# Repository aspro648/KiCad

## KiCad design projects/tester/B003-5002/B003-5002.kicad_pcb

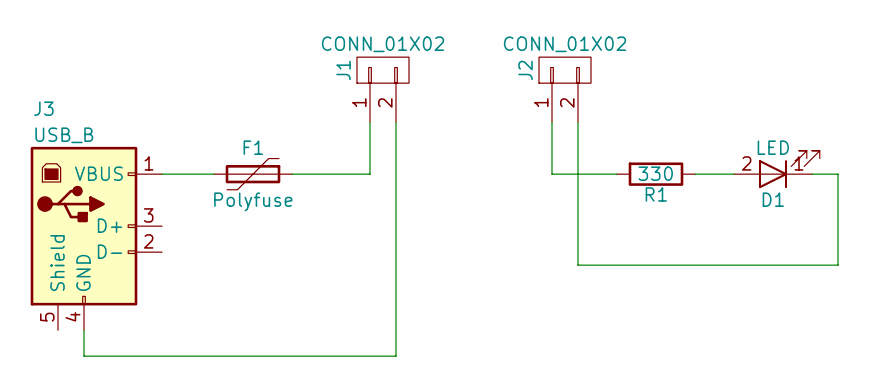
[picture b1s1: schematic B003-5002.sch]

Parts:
D1: LED; LED_D3.0mm
F1: Polyfuse; Fuse_Littelfuse-LVR100
J1: CONN_01X02; Molex_Microfit3_Header_02x01_Angled_43045-020x
J2: CONN_01X02; Molex_NanoFit_1x02x2.50mm_Angled
J3: USB_B
R1: 330; R_Axial_DIN0207_L6.3mm_D2.5mm_P7.62mm_Horizontal

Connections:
unnamed: D1.1 (K), J2.2
unnamed: D1.2 (A), R1.1
unnamed: F1.1, J1.1
unnamed: F1.2, J3.1 (VBUS)
unnamed: J1.2, J3.4 (GND)
unnamed: J2.1, R1.2

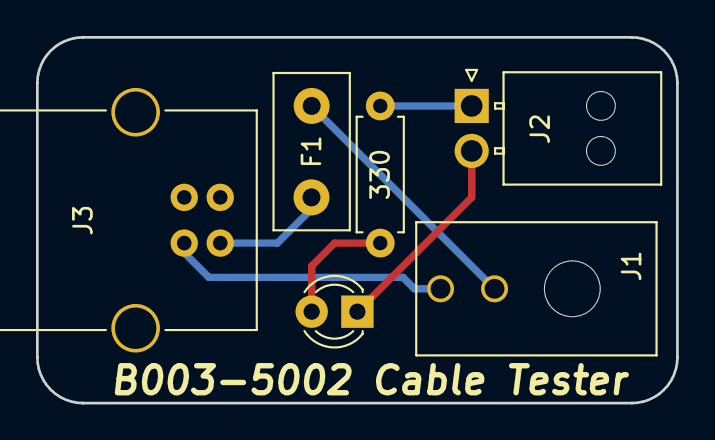
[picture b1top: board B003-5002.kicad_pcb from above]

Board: 2 copper layers, 35.6 x 20.3 mm, 6 parts (0 on the bottom side), 6 nets.

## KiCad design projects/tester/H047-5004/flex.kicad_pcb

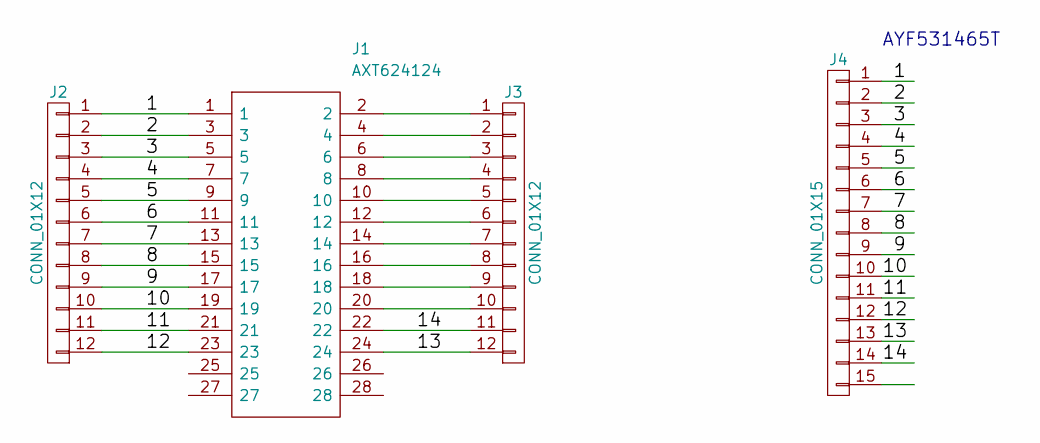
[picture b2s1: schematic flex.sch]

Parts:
J1: AXT624124; Mouser Part Number 769-AXT624124
J2, J3: CONN_01X12; Pin_Header_Straight_1x12_Pitch1.27mm
J4: CONN_01X15

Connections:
/1: J1.1, J2.1, J4.1
/2: J1.3, J2.2, J4.2
/3: J1.5, J2.3, J4.3
/4: J1.7, J2.4, J4.4
/5: J1.9, J2.5, J4.5
/6: J1.11, J2.6, J4.6
/7: J1.13, J2.7, J4.7
/8: J1.15, J2.8, J4.8
/9: J1.17, J2.9, J4.9
/10: J1.19, J2.10, J4.10
/11: J1.21, J2.11, J4.11
/12: J1.23, J2.12, J4.12
/13: J1.24, J3.12, J4.13
/14: J1.22, J3.11, J4.14
unnamed: J1.2, J3.1
unnamed: J1.4, J3.2
unnamed: J1.6, J3.3
unnamed: J1.8, J3.4
unnamed: J1.10, J3.5
unnamed: J1.12, J3.6
unnamed: J1.14, J3.7
unnamed: J1.16, J3.8
unnamed: J1.18, J3.9
unnamed: J1.20, J3.10

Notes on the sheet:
AYF531465T

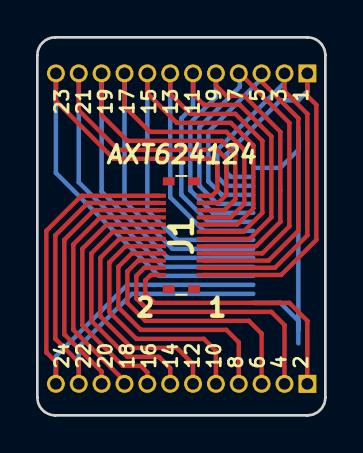
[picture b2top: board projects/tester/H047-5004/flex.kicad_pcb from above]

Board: 2 copper layers, 16.0 x 21.0 mm, 4 parts (1 on the bottom side), 24 nets.

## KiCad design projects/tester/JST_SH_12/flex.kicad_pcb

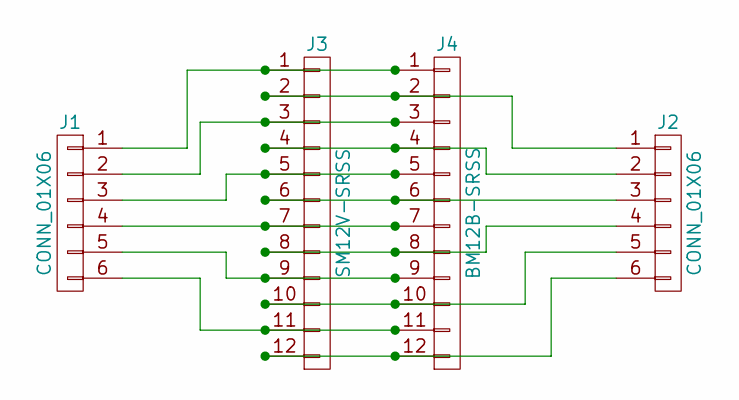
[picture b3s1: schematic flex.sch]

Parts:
J1, J2: CONN_01X06; Pin_Header_Straight_1x06_Pitch2.54mm
J3: SM12V-SRSS; JST_SH_SM12B-SRSS-TB_12x1.00mm_Angled
J4: BM12B-SRSS; JST_SH_BM12B-SRSS-TB_12x1.00mm_Straight

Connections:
unnamed: J1.1, J3.1, J4.1
unnamed: J1.2, J3.3, J4.3
unnamed: J1.3, J3.5, J4.5
unnamed: J1.4, J3.7, J4.7
unnamed: J1.5, J3.9, J4.9
unnamed: J1.6, J3.11, J4.11
unnamed: J2.1, J3.2, J4.2
unnamed: J2.2, J3.4, J4.4
unnamed: J2.3, J3.6, J4.6
unnamed: J2.4, J3.8, J4.8
unnamed: J2.5, J3.10, J4.10
unnamed: J2.6, J3.12, J4.12

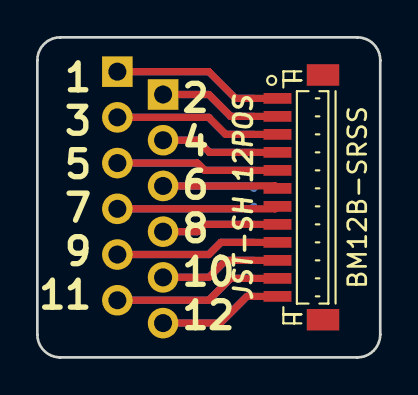
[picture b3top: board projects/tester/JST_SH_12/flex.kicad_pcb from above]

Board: 2 copper layers, 19.1 x 17.8 mm, 4 parts (1 on the bottom side), 12 nets.

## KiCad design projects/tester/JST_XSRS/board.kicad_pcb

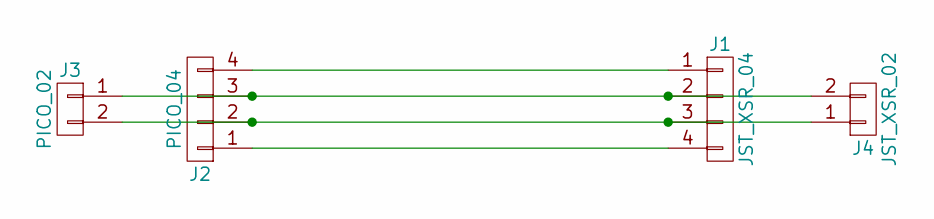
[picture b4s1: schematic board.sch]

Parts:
J1: JST_XSR_04; JST_SH_BM04B-SRSS-TB_04x1.00mm_Straight
J2: PICO_04; Molex_PicoBlade_53048-0410_04x1.25mm_Angled
J3: PICO_02; Molex_PicoBlade_53048-0210_02x1.25mm_Angled
J4: JST_XSR_02; JST_SH_BM02B-SRSS-TB_02x1.00mm_Straight

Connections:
unnamed: J1.1, J2.4
unnamed: J1.2, J2.3, J3.1, J4.2
unnamed: J1.3, J2.2, J3.2, J4.1
unnamed: J1.4, J2.1

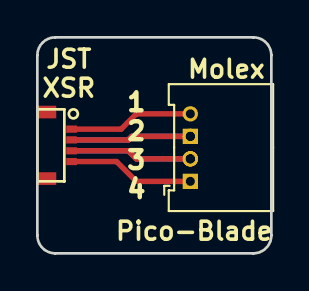
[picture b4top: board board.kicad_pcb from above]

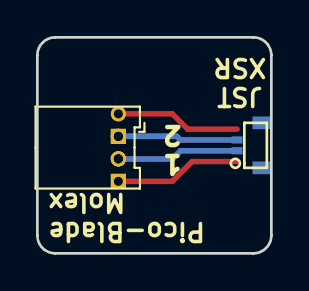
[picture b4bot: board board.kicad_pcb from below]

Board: 2 copper layers, 13.0 x 12.0 mm, 4 parts (2 on the bottom side), 4 nets.

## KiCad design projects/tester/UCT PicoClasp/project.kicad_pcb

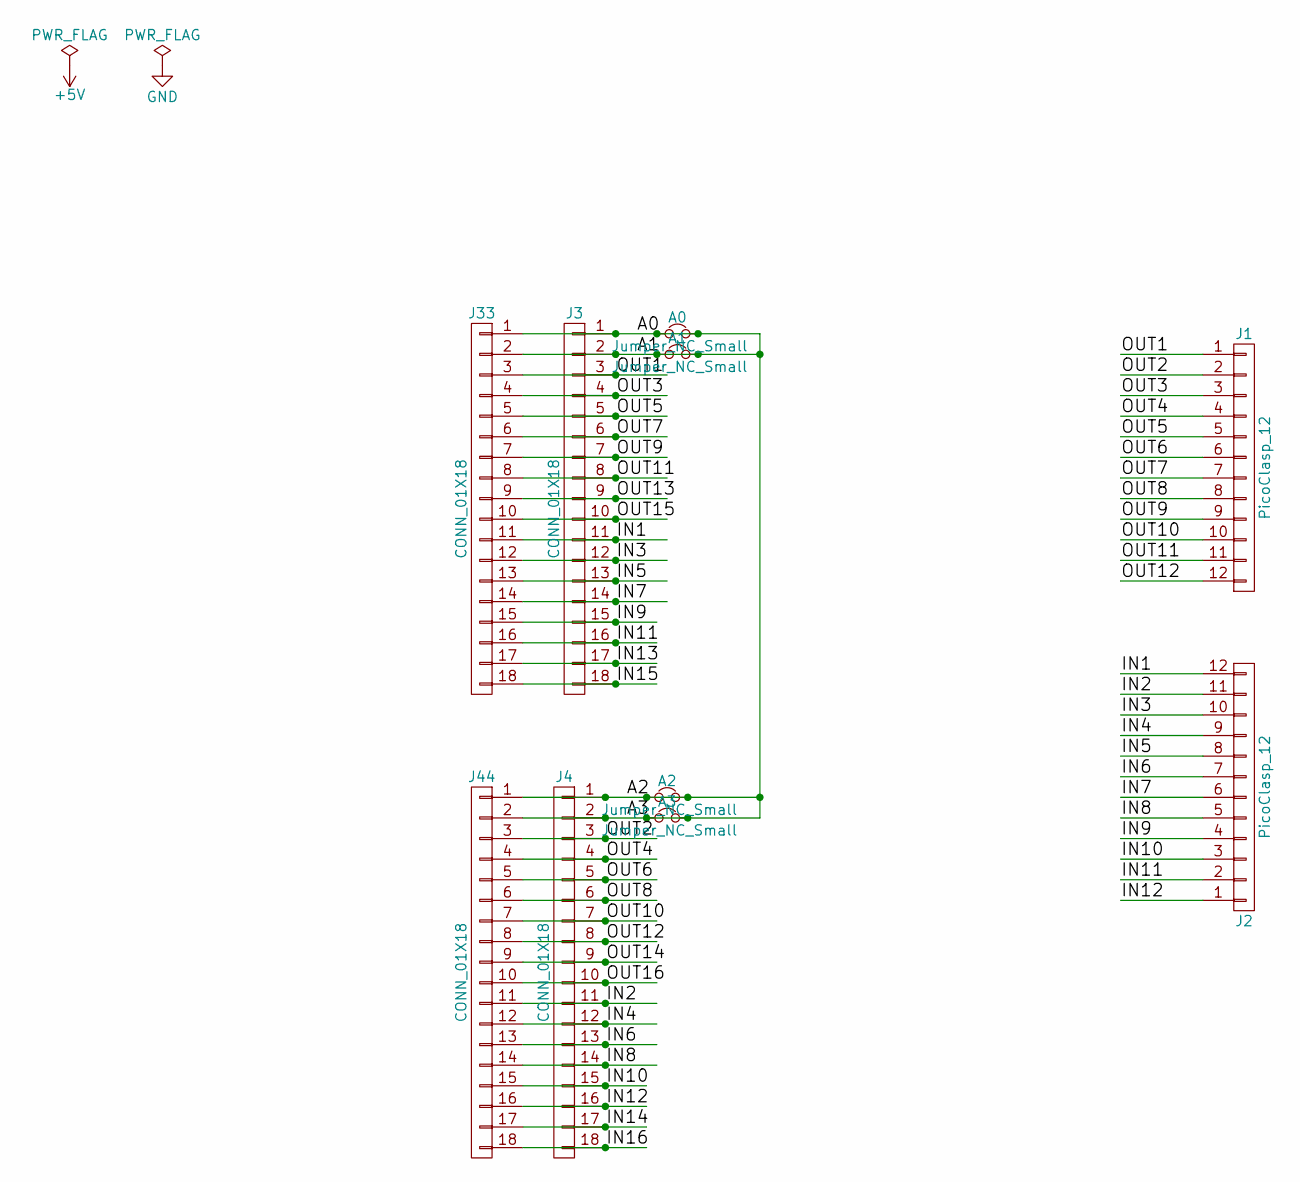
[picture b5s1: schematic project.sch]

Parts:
A0, A1, A2, A3: Jumper_NC_Small; R_0805_HandSoldering
J1, J2: PicoClasp_12; Molex_PicoClasp_501331-1207_1x12_P1.0mm_Vertical
J3, J4, J33, J44: CONN_01X18; Pin_Header_Straight_1x18_Pitch2.54mm

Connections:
/A0: A0.1, A0.2, A1.1, A1.2, A2.1, A2.2, A3.1, A3.2, J3.1, J3.2, J4.1, J4.2, J33.1, J33.2, J44.1, J44.2
/IN1: J2.12, J3.11, J33.11
/IN2: J2.11, J4.11, J44.11
/IN3: J2.10, J3.12, J33.12
/IN4: J2.9, J4.12, J44.12
/IN5: J2.8, J3.13, J33.13
/IN6: J2.7, J4.13, J44.13
/IN7: J2.6, J3.14, J33.14
/IN8: J2.5, J4.14, J44.14
/IN9: J2.4, J3.15, J33.15
/IN10: J2.3, J4.15, J44.15
/IN11: J2.2, J3.16, J33.16
/IN12: J2.1, J4.16, J44.16
/IN13: J3.17, J33.17
/IN14: J4.17, J44.17
/IN15: J3.18, J33.18
/IN16: J4.18, J44.18
/OUT1: J1.1, J3.3, J33.3
/OUT2: J1.2, J4.3, J44.3
/OUT3: J1.3, J3.4, J33.4
/OUT4: J1.4, J4.4, J44.4
/OUT5: J1.5, J3.5, J33.5
/OUT6: J1.6, J4.5, J44.5
/OUT7: J1.7, J3.6, J33.6
/OUT8: J1.8, J4.6, J44.6
/OUT9: J1.9, J3.7, J33.7
/OUT10: J1.10, J4.7, J44.7
/OUT11: J1.11, J3.8, J33.8
/OUT12: J1.12, J4.8, J44.8
/OUT13: J3.9, J33.9
/OUT14: J4.9, J44.9
/OUT15: J3.10, J33.10
/OUT16: J4.10, J44.10

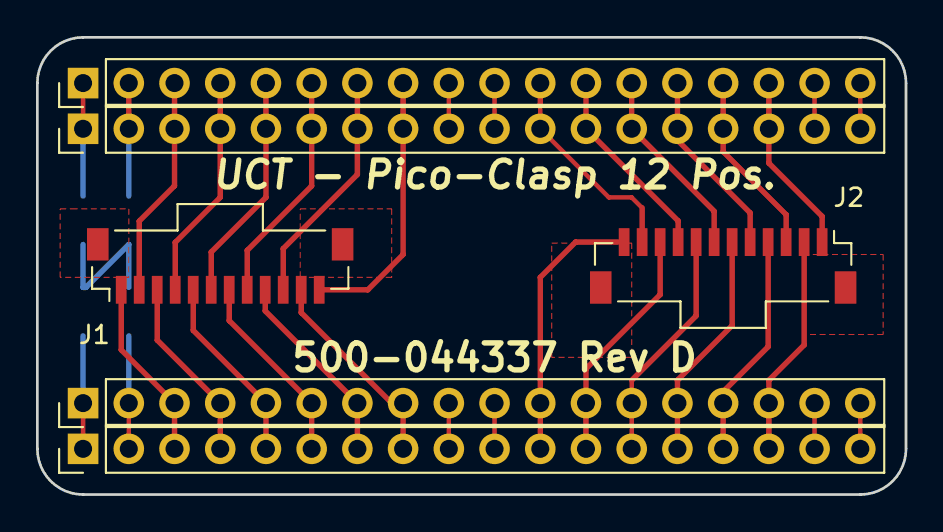
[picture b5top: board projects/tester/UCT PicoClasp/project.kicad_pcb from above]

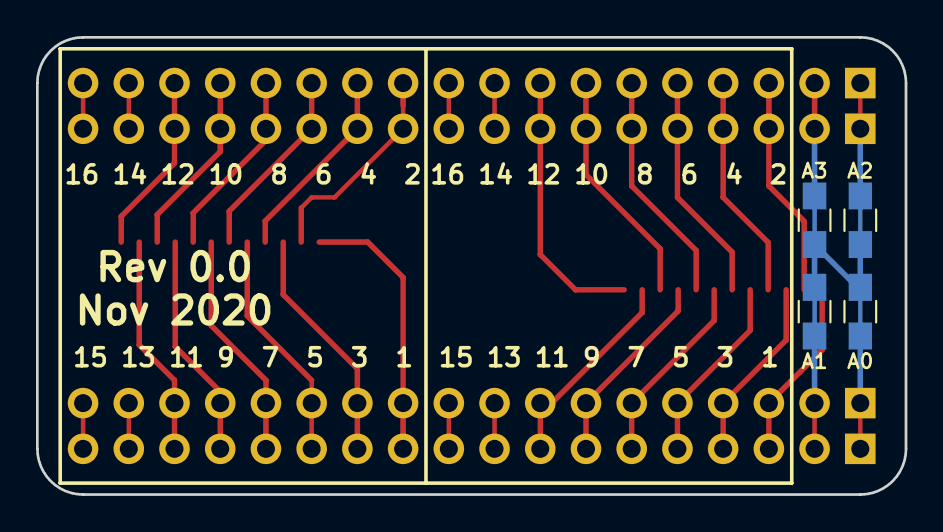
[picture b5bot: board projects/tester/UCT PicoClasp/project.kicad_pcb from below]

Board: 2 copper layers, 48.3 x 25.4 mm, 10 parts (4 on the bottom side), 33 nets.

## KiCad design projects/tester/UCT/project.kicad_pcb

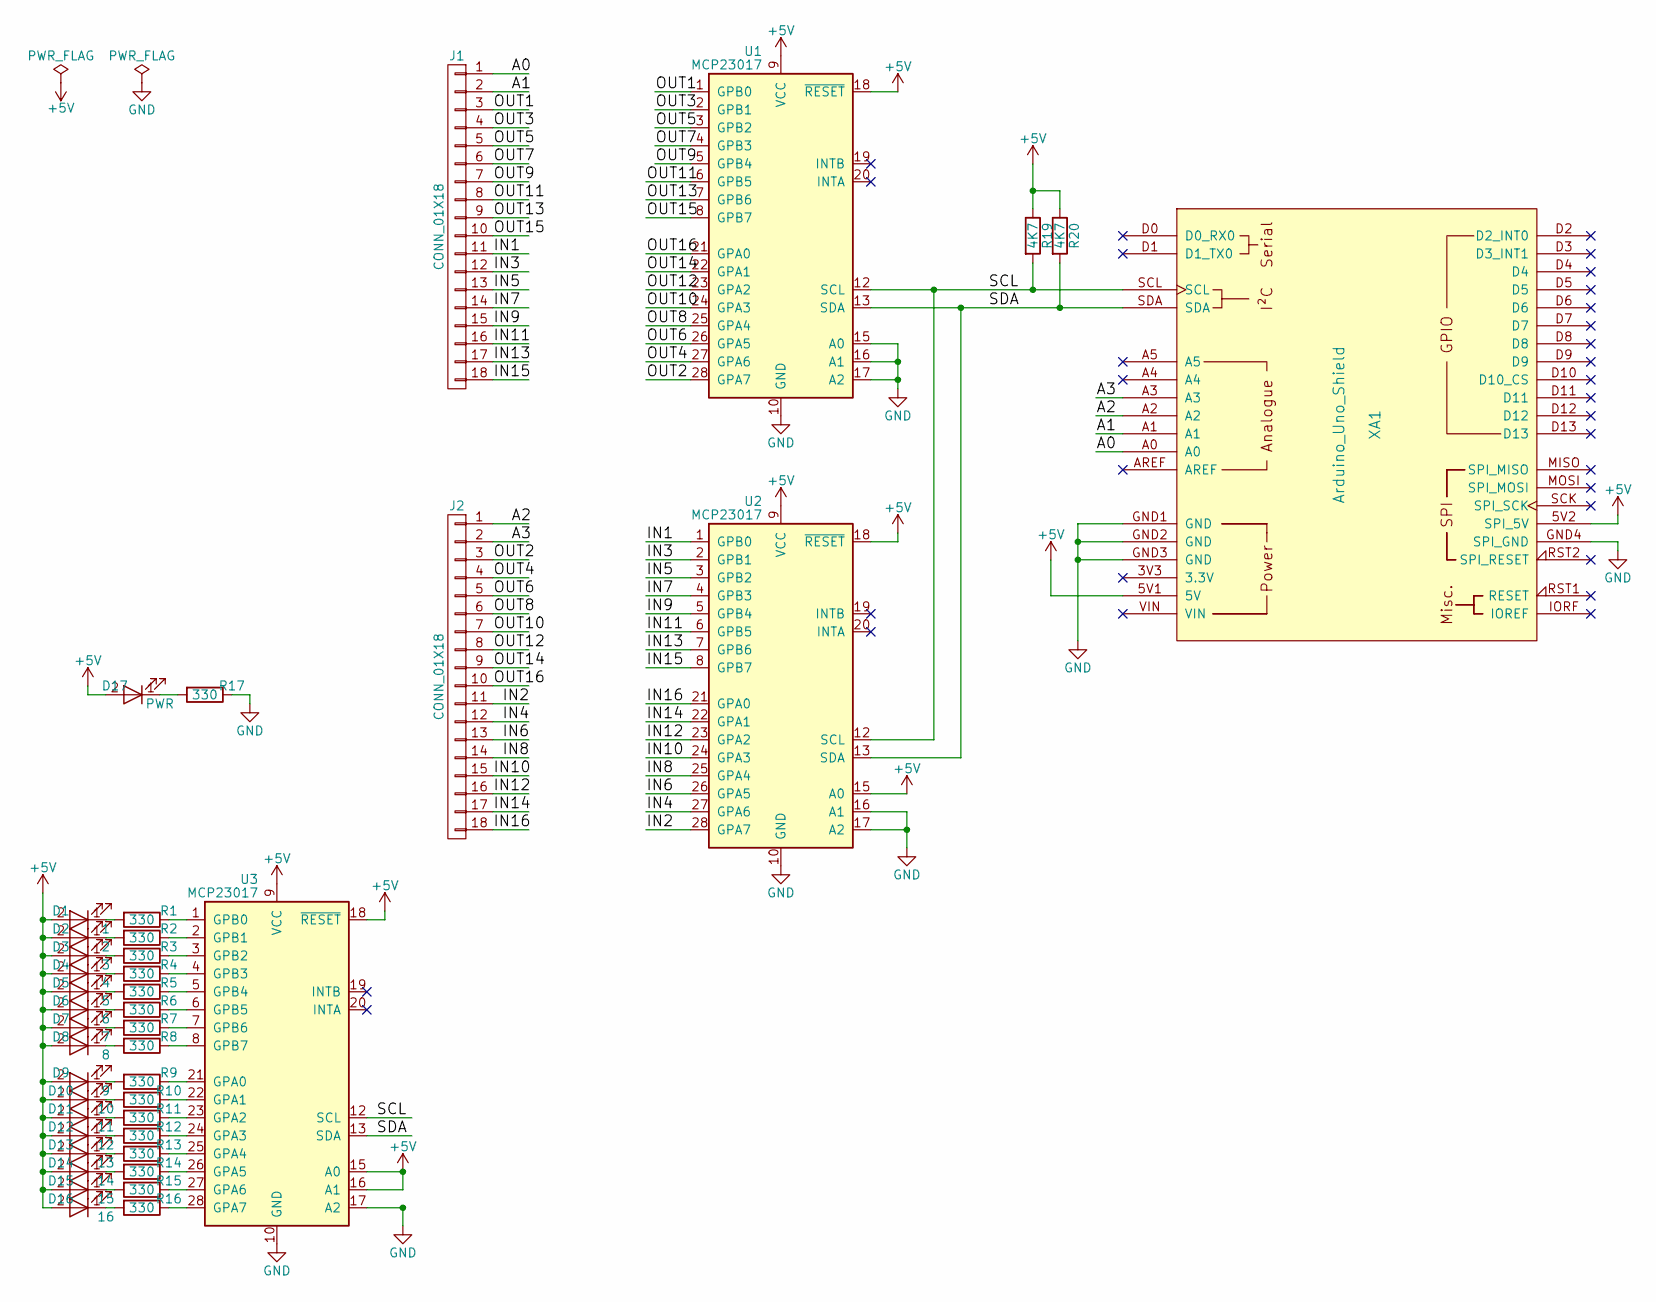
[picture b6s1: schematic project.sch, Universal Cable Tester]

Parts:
D1: 1; LED_0805_HandSoldering
D2: 2; LED_0805_HandSoldering
D3: 3; LED_0805_HandSoldering
D4: 4; LED_0805_HandSoldering
D5: 5; LED_0805_HandSoldering
D6: 6; LED_0805_HandSoldering
D7: 7; LED_0805_HandSoldering
D8: 8; LED_0805_HandSoldering
D9: 9; LED_0805_HandSoldering
D10: 10; LED_0805_HandSoldering
D11: 11; LED_0805_HandSoldering
D12: 12; LED_0805_HandSoldering
D13: 13; LED_0805_HandSoldering
D14: 14; LED_0805_HandSoldering
D15: 15; LED_0805_HandSoldering
D16: 16; LED_0805_HandSoldering
D17: PWR; LED_0805_HandSoldering
J1, J2: CONN_01X18; Pin_Header_Straight_1x18_Pitch2.54mm
R1, R2, R3, R4, R5, R6, R7, R8, R9, R10, R11, R12, R13, R14, R15, R16, R17: 330; R_0805_HandSoldering
R19, R20: 4K7; R_0805_HandSoldering
U1, U2, U3: MCP23017; SSOP-28_5.3x10.2mm_Pitch0.65mm
XA1: Arduino_Uno_Shield

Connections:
+5V: D1.2 (A), D2.2 (A), D3.2 (A), D4.2 (A), D5.2 (A), D6.2 (A), D7.2 (A), D8.2 (A), D9.2 (A), D10.2 (A), D11.2 (A), D12.2 (A), D13.2 (A), D14.2 (A), D15.2 (A), D16.2 (A), D17.2 (A), R19.1, R20.1, U1.9 (VCC), U1.18 (~RESET), U2.9 (VCC), U2.15 (A0), U2.18 (~RESET), U3.9 (VCC), U3.15 (A0), U3.16 (A1), U3.18 (~RESET), XA1.5V1 (5V), XA1.5V2 (SPI_5V)
/A0: J1.1, XA1.A0
/A1: J1.2, XA1.A1
/A2: J2.1, XA1.A2
/A3: J2.2, XA1.A3
/IN1: J1.11, U2.1 (GPB0)
/IN2: J2.11, U2.28 (GPA7)
/IN3: J1.12, U2.2 (GPB1)
/IN4: J2.12, U2.27 (GPA6)
/IN5: J1.13, U2.3 (GPB2)
/IN6: J2.13, U2.26 (GPA5)
/IN7: J1.14, U2.4 (GPB3)
/IN8: J2.14, U2.25 (GPA4)
/IN9: J1.15, U2.5 (GPB4)
/IN10: J2.15, U2.24 (GPA3)
/IN11: J1.16, U2.6 (GPB5)
/IN12: J2.16, U2.23 (GPA2)
/IN13: J1.17, U2.7 (GPB6)
/IN14: J2.17, U2.22 (GPA1)
/IN15: J1.18, U2.8 (GPB7)
/IN16: J2.18, U2.21 (GPA0)
/OUT1: J1.3, U1.1 (GPB0)
/OUT2: J2.3, U1.28 (GPA7)
/OUT3: J1.4, U1.2 (GPB1)
/OUT4: J2.4, U1.27 (GPA6)
/OUT5: J1.5, U1.3 (GPB2)
/OUT6: J2.5, U1.26 (GPA5)
/OUT7: J1.6, U1.4 (GPB3)
/OUT8: J2.6, U1.25 (GPA4)
/OUT9: J1.7, U1.5 (GPB4)
/OUT10: J2.7, U1.24 (GPA3)
/OUT11: J1.8, U1.6 (GPB5)
/OUT12: J2.8, U1.23 (GPA2)
/OUT13: J1.9, U1.7 (GPB6)
/OUT14: J2.9, U1.22 (GPA1)
/OUT15: J1.10, U1.8 (GPB7)
/OUT16: J2.10, U1.21 (GPA0)
/SCL: R19.2, U1.12 (SCL), U2.12 (SCL), U3.12 (SCL), XA1.SCL
/SDA: R20.2, U1.13 (SDA), U2.13 (SDA), U3.13 (SDA), XA1.SDA
GND: R17.1, U1.10 (GND), U1.15 (A0), U1.16 (A1), U1.17 (A2), U2.10 (GND), U2.16 (A1), U2.17 (A2), U3.10 (GND), U3.17 (A2), XA1.GND1 (GND), XA1.GND2 (GND), XA1.GND3 (GND), XA1.GND4 (SPI_GND)
unnamed: D1.1 (K), R1.2
unnamed: D2.1 (K), R2.2
unnamed: D3.1 (K), R3.2
unnamed: D4.1 (K), R4.2
unnamed: D5.1 (K), R5.2
unnamed: D6.1 (K), R6.2
unnamed: D7.1 (K), R7.2
unnamed: D8.1 (K), R8.2
unnamed: D9.1 (K), R9.2
unnamed: D10.1 (K), R10.2
unnamed: D11.1 (K), R11.2
unnamed: D12.1 (K), R12.2
unnamed: D13.1 (K), R13.2
unnamed: D14.1 (K), R14.2
unnamed: D15.1 (K), R15.2
unnamed: D16.1 (K), R16.2
unnamed: D17.1 (K), R17.2
unnamed: R1.1, U3.1 (GPB0)
unnamed: R2.1, U3.2 (GPB1)
unnamed: R3.1, U3.3 (GPB2)
unnamed: R4.1, U3.4 (GPB3)
unnamed: R5.1, U3.5 (GPB4)
unnamed: R6.1, U3.6 (GPB5)
unnamed: R7.1, U3.7 (GPB6)
unnamed: R8.1, U3.8 (GPB7)
unnamed: R9.1, U3.21 (GPA0)
unnamed: R10.1, U3.22 (GPA1)
unnamed: R11.1, U3.23 (GPA2)
unnamed: R12.1, U3.24 (GPA3)
unnamed: R13.1, U3.25 (GPA4)
unnamed: R14.1, U3.26 (GPA5)
unnamed: R15.1, U3.27 (GPA6)
unnamed: R16.1, U3.28 (GPA7)

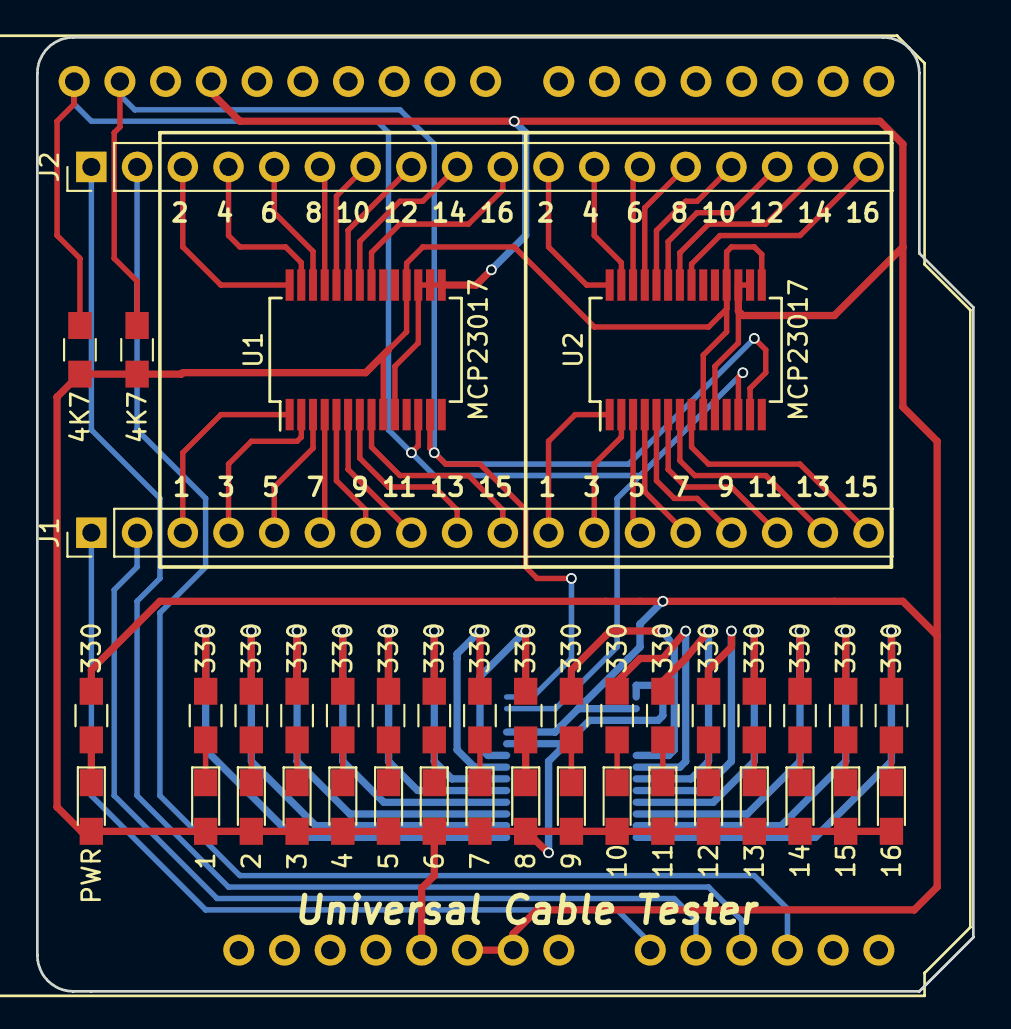
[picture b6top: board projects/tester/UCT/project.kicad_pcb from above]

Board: 2 copper layers, 52.0 x 53.0 mm, 42 parts (1 on the bottom side), 73 nets.

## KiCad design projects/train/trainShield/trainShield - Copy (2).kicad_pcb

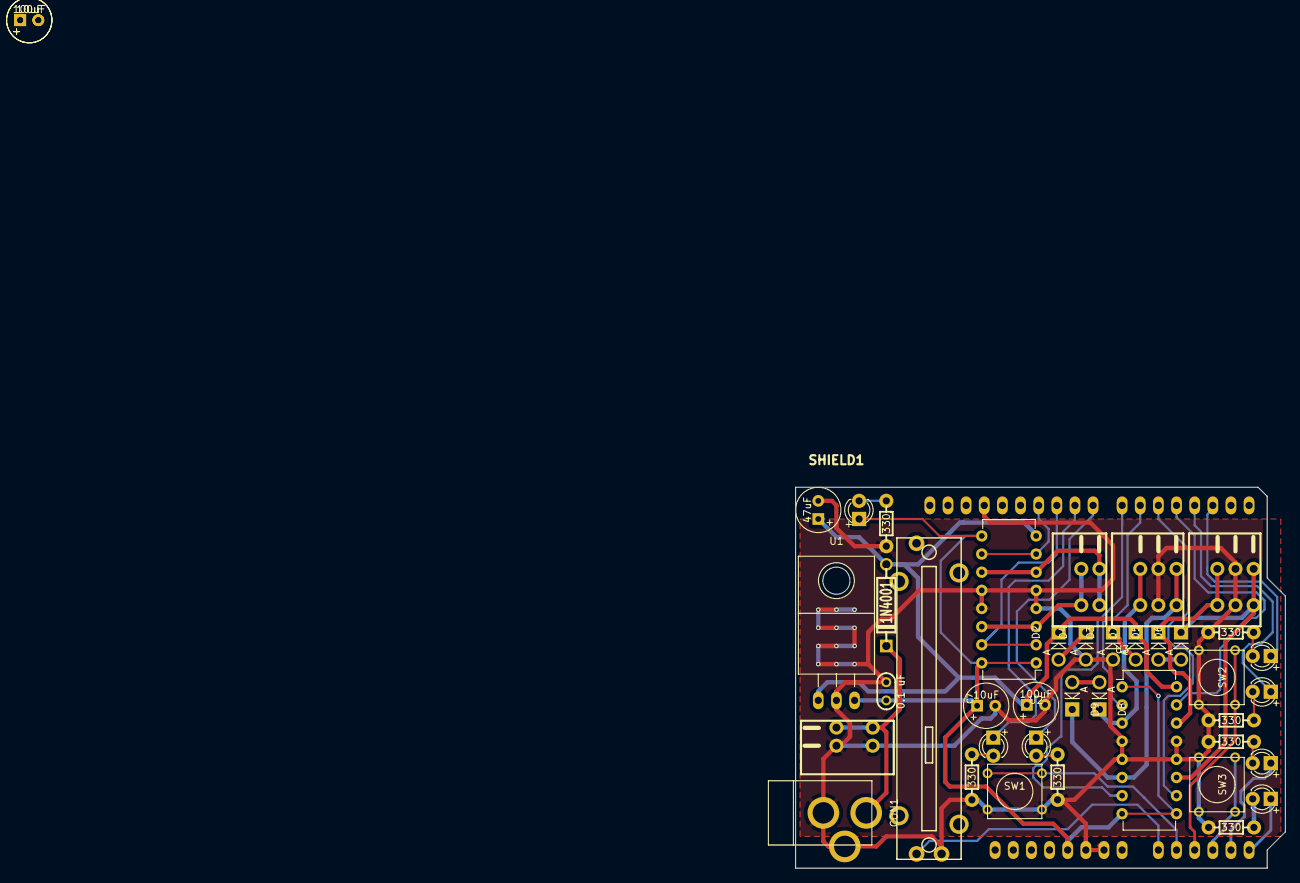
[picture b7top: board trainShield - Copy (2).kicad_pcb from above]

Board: 2 copper layers, 68.6 x 53.3 mm, 42 parts (0 on the bottom side), 37 nets.

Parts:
C1: 0.1 uF; C1
C2: 47uF; C2
C3, C5: 100uF; C2
C4, C6: 10uF; C2
C7: CTRIM; BOURNS-PTA3043_30mm-slide-pot
CON1: BARREL_JACK
D1: 1N4001
D2, D3, D4, D5, D6, D7, D8, D9: 1N4001; Diode_DO-41_SOD81_Vertical_AnodeUp
D10, D11, D12, D13, D14, D15, D16: LED; LED-3MM
P1, P3: TERM_2; TERMx2
P2, P4: TERMx3
R1, R2, R3, R4, R5, R6, R7: 330; Resistor_Horz
SHIELD1: ARDUINO_SHIELD
SW1, SW2, SW3: SW_PUSHBUTTON; SW_PUSH_SMALL
U1: 7805; TO-220_Neutral123_Horizontal
U2, U3: L293D; DIP-16_W7.62mm

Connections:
+5V: C1.1, C4.1, C6.1, D12.2, SHIELD1.5V, U1.VO, U2.1, U2.9, U2.16, U3.1, U3.8, U3.9
+12V: C2.1, C3.1, C5.1, D1.1, D2.1, D7.1, U1.VI, U2.8, U3.16
/MOT_A: SHIELD1.11, U2.7, U2.10
/MOT_B: SHIELD1.10, U2.2, U2.15
/M_1: P1.1, U2.6, U2.11
/M_2: P1.2, U2.3, U2.14
/TURN_1_A: SHIELD1.4, U3.15
/TURN_1_B: SHIELD1.5, U3.10
/TURN_2_A: SHIELD1.6, U3.2
/TURN_2_B: SHIELD1.7, U3.7
GND: C1.2, C2.2, C3.2, C4.2, C5.2, C6.2, C7.2, CON1.2, CON1.3, D3.2, D4.2, P2.2, P3.2, P4.2, R1.1, R2.1, R3.1, R4.1, R5.1, R6.1, R7.1, SHIELD1.GND1, SHIELD1.GND2, SHIELD1.GND3, SW1.2, SW2.2, SW3.2, U1.GND, U2.4, U2.5, U2.12, U2.13, U3.4, U3.5, U3.12, U3.13
unnamed: C7.1, SHIELD1.AD0
unnamed: CON1.1, D1.2, P3.1
unnamed: D2.2, D4.1
unnamed: D3.1, D7.2
unnamed: D5.1, P2.3, U3.14
unnamed: D5.2, D6.2
unnamed: D6.1, P2.1, U3.11
unnamed: D8.1, P4.3, U3.3
unnamed: D8.2, D9.2
unnamed: D9.1, P4.1, U3.6
unnamed: D10.1, R5.2
unnamed: D10.2, SHIELD1.8
unnamed: D11.1, R6.2
unnamed: D11.2, SHIELD1.9
unnamed: D12.1, R1.2
unnamed: D13.1, R2.2
unnamed: D13.2, SHIELD1.2
unnamed: D14.1, R3.2
unnamed: D14.2, SHIELD1.3
unnamed: D15.1, R4.2
unnamed: D15.2, SHIELD1.AD4
unnamed: D16.1, R7.2
unnamed: D16.2, SHIELD1.AD5
unnamed: SHIELD1.AD1, SW1.1
unnamed: SHIELD1.AD2, SW2.1
unnamed: SHIELD1.AD3, SW3.1
